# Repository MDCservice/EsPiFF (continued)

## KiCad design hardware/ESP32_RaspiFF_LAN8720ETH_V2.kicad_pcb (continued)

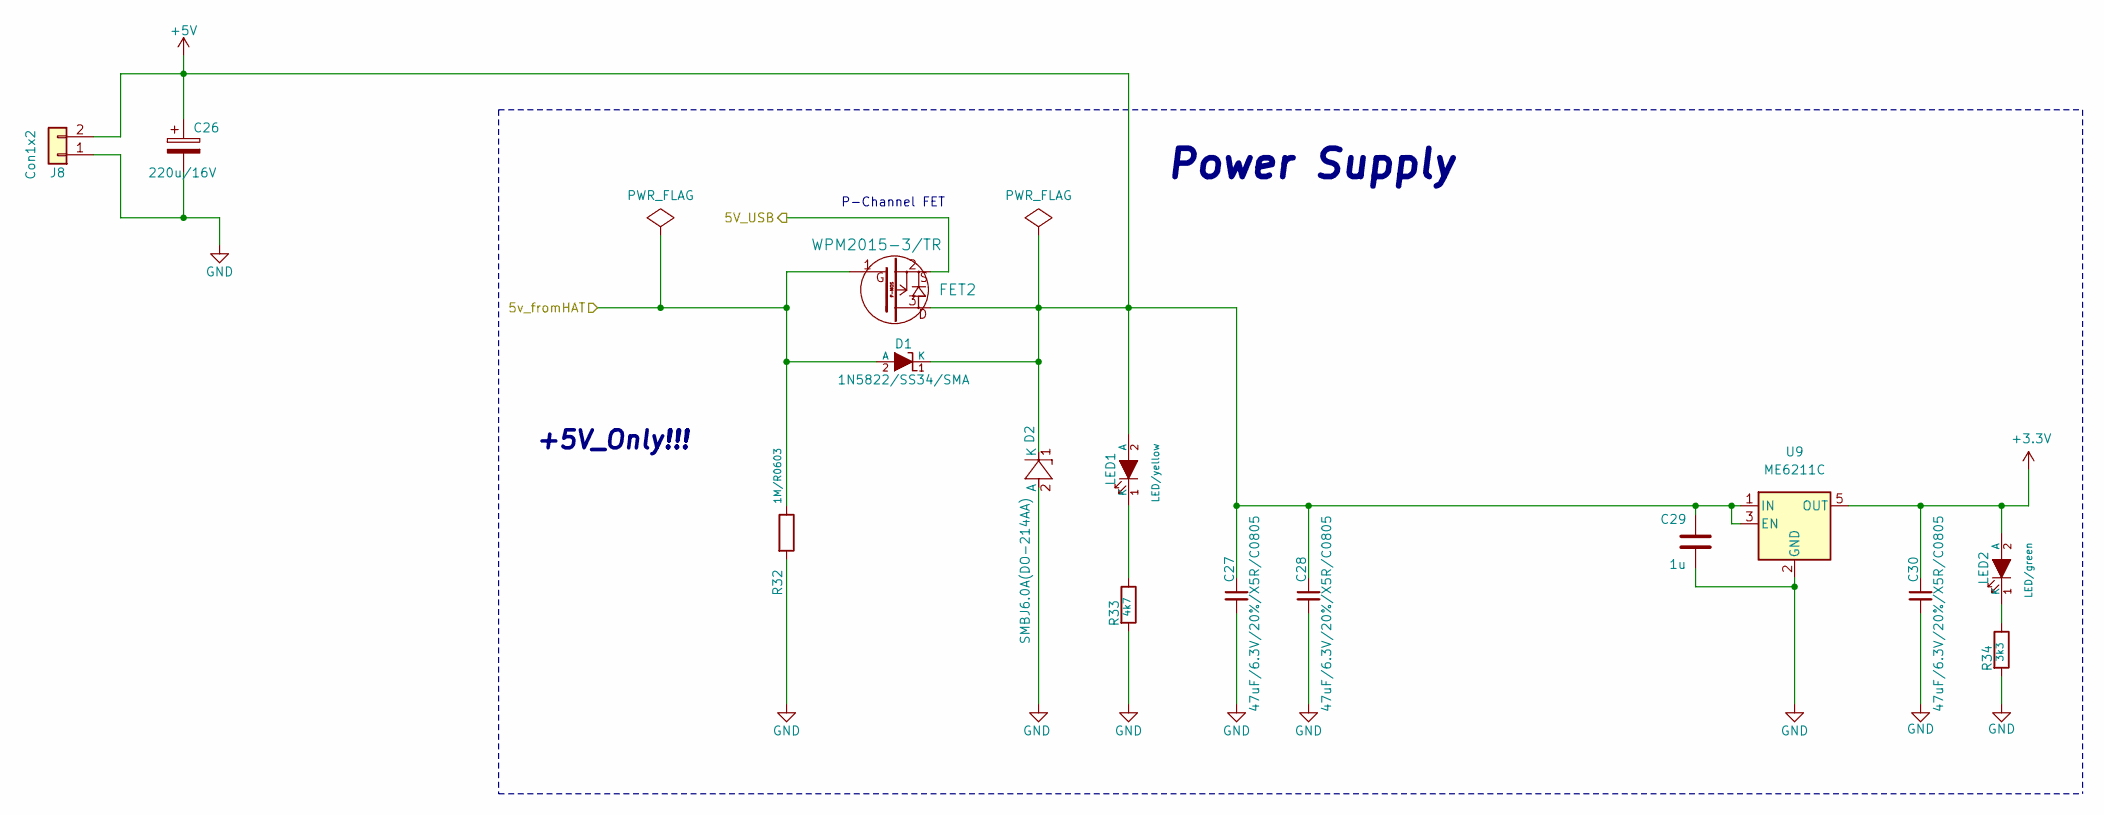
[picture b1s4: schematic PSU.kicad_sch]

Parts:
C26: 220u/16V; CP_Elec_6.3x7.7
C27, C28, C30: 47uF/6.3V/20%/X5R/C0805; C_0805_5MIL_DWS
C29: 1u; C_0603_1608Metric
D1: 1N5822/SS34/SMA; SMA-KA
D2: SMBJ6.0A(DO-214AA); DO214AA_1(K)-2(A)
FET2: WPM2015-3/TR; SOT23
J8: Con1x2; KF301-5.0-2P
LED1: LED/yellow; LED_0603_1608Metric
LED2: LED/green; LED_0603_1608Metric
R32: 1M/R0603; R_0603_1608Metric
R33: 4k7; R_0603_1608Metric
R34: 3k3; R_0603_1608Metric
U9: ME6211C; SOT-23-5

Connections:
+3V3: C30.1, LED2.2 (A), U9.5 (OUT); also elsewhere on the board
+5V: C26.1, C27.1, C28.1, C29.1, D1.1 (K), D2.1 (K), FET2.3, J8.2, LED1.2 (A), U9.1 (IN), U9.3 (EN); also elsewhere on the board
/5V_from_HAT: D1.2 (A), FET2.1, R32.1; also elsewhere on the board
/PSU/5V_USB: FET2.2; also elsewhere on the board
GND: C26.2, C27.2, C28.2, C29.2, C30.2, D2.2 (A), J8.1, R32.2, R33.2, R34.2, U9.2 (GND); also elsewhere on the board
unnamed: LED1.1 (K), R33.1
unnamed: LED2.1 (K), R34.1

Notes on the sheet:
Power Supply
+5V_Only!!!
P-Channel FET

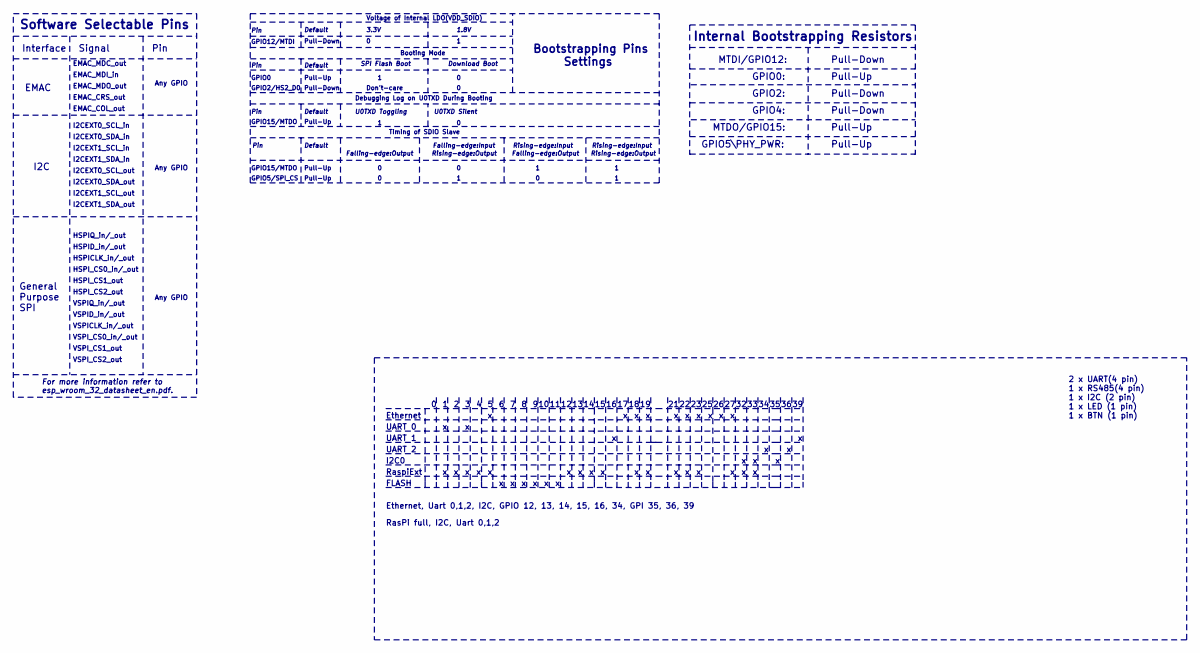
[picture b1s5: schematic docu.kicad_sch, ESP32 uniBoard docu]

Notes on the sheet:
GPIO15/MTDO
HSPID_in/_out
I2C0
Ethernet, Uart 0,1,2, I2C, GPIO 12, 13, 14, 15, 16, 34, GPI 35, 36, 39
EMAC_MDC_out
GPIO2:
GPIO0:
I2CEXT1_SCL_in
I2CEXT1_SDA_out
Any GPIO
I2CEXT0_SCL_out
Pull-Up
Pin
GPIO5/SPI_CS
GPIO0
Voltage of Internal LDO(VDD_SDIO)
VSPID_in/_out
VSPI_CS0_in/_out
Falling-edge:Input
I2CEXT0_SCL_in
UART 0
HSPI_CS0_in/_out
Interface
I2CEXT1_SCL_out
I2CEXT0_SDA_in
RasPi full, I2C, Uart 0,1,2
Rising-edge:Input
HSPI_CS1_out
Default
MTDI/GPIO12:
Pull-Down
Falling-edge:Output
VSPI_CS2_out
MTDO/GPIO15:
EMAC_MDI_in
U0TXD Silent
EMAC_MDO_out
HSPICLK_in/_out
Internal Bootstrapping Resistors
Booting Mode

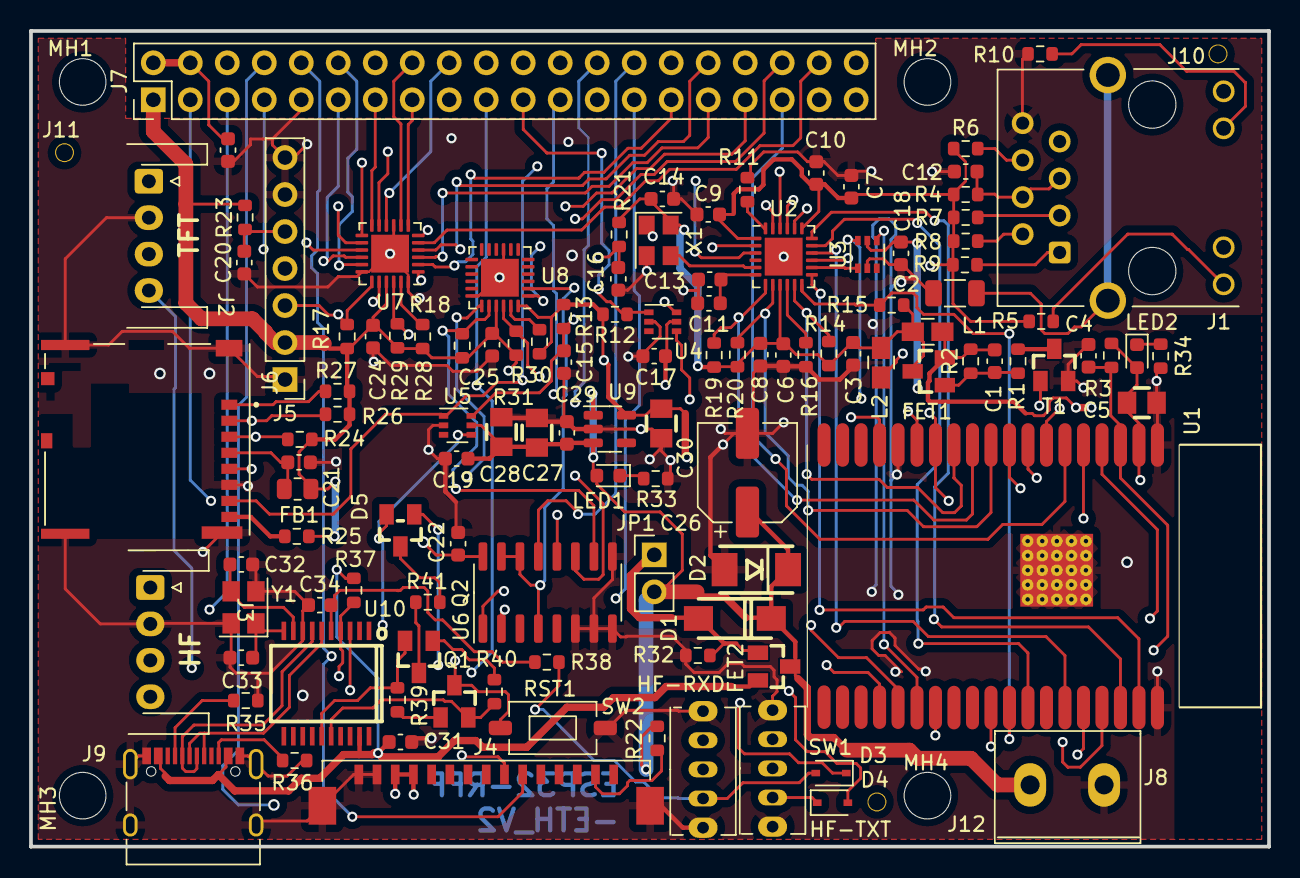
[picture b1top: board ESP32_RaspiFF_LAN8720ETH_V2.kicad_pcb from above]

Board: 4 copper layers, 85.0 x 56.0 mm, 122 parts (0 on the bottom side), 103 nets.

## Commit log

2022-05-23 initaial check in EsPiFF V2 files
2022-05-23 initial check in firmware files
2022-05-23 update headline
2022-05-23 initial check in license.txt
2022-05-23 initial check in EsPiFF photos
2022-05-23 correct typos
2022-05-23 added EsPiFF Version 1 pictures
2022-05-23 added pictures for Version 1
2022-05-24 added HMI example pictures
2022-05-24 add HMI and Rain RFID picture
2022-05-24 Update Readme.md, added example HMI, HF-, RAIN-
2022-05-24 add photo of opend HMI enclosure
2022-05-25 replace files with copyright header and Doxygen comments
2022-05-25 added drivers in own folder
2022-05-25 add project files for root folder
2022-05-26 initial check in Cafon UHF RFID driver for the MU80x series
2022-05-26 move MU80x to drivers
2022-05-26 moved MU80 from libs to drivers
2022-05-26 initial check in libpq_esp32 files
2022-05-26 check in SD-card drivers and test
2022-05-26 Initial check in HMI driver
2022-06-22 initial upload espiff-v3 annotated
2022-06-22 Update Readme, fix some typos, add V3 board picture
2022-06-22 fix typos, add EtherSIB
2022-06-22 fix typo
2022-06-22 change board-v3 picture
2022-06-22 add picture for V2 board
2022-07-20 initial check in V3 schematic and PCB rendering
2022-07-20 re-uploaded V3 schematic after correcting typos
2022-07-27 low res pictures for now
2022-07-27 replace with high-res picture
2022-07-27 check in high-res photos
2022-10-01 Create ReadMe.md
    archived V3.0 files
2022-10-01 removed V3.0 hardware folder, replace by V3.1
2022-10-01 Upload V3.1 final version
2022-10-01 Updated info on V3.1
2022-10-12 initiail upload v.31 photos
2022-10-27 add info about not use the PCB antenna,
    but an external antenna instead
2022-11-02 replace PDF,
    correct spelling
2022-11-02 update PDF
    spelling
2022-11-09 update to v0.3 of the datasheet
2022-11-09 change to datasheet version 0.3
    added info about the cable set, color code of cables, pinout
2022-11-10 added CE info
    CE and safety info included into the datasheet
2022-11-16 Update README.md
    added details to the communication between ESP32 and RP2040
2022-11-18 Add files via upload
    added simplified CE+UK DoC
2022-11-23 replaced with v0.5
2022-11-23 update ESP32 to RP2040 interconnection
2022-11-24 add PCB antenna news
2023-05-12 initial upload the dual language version
2023-05-12 inital upload of the dual language version
